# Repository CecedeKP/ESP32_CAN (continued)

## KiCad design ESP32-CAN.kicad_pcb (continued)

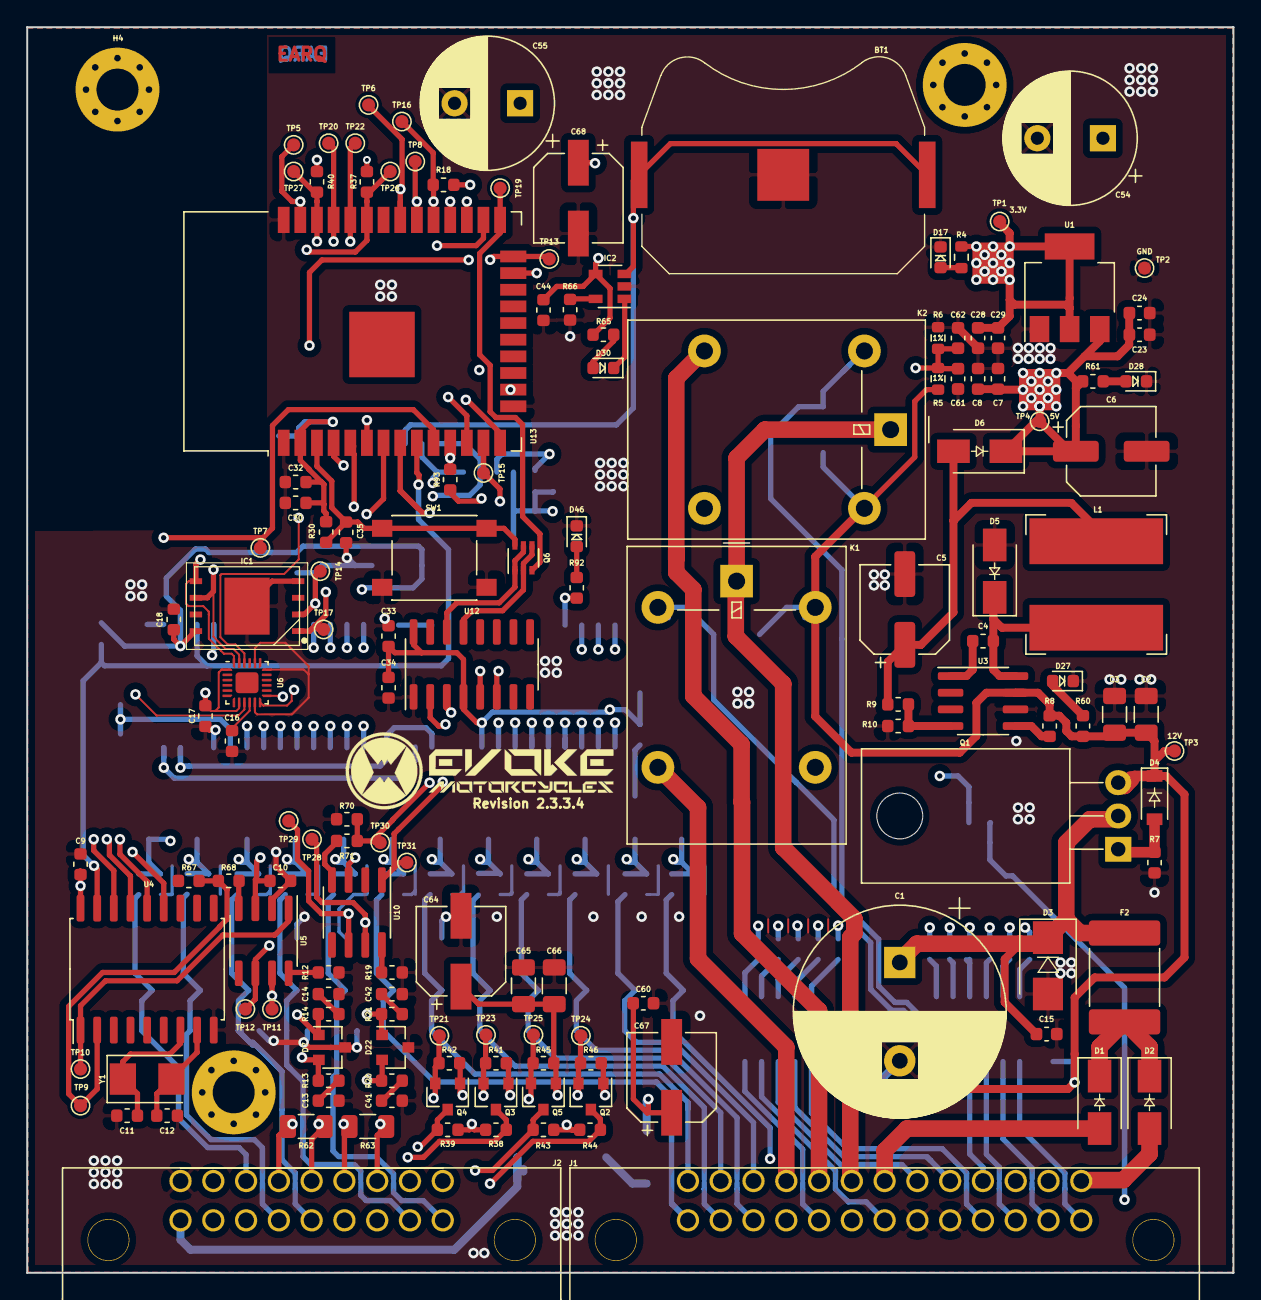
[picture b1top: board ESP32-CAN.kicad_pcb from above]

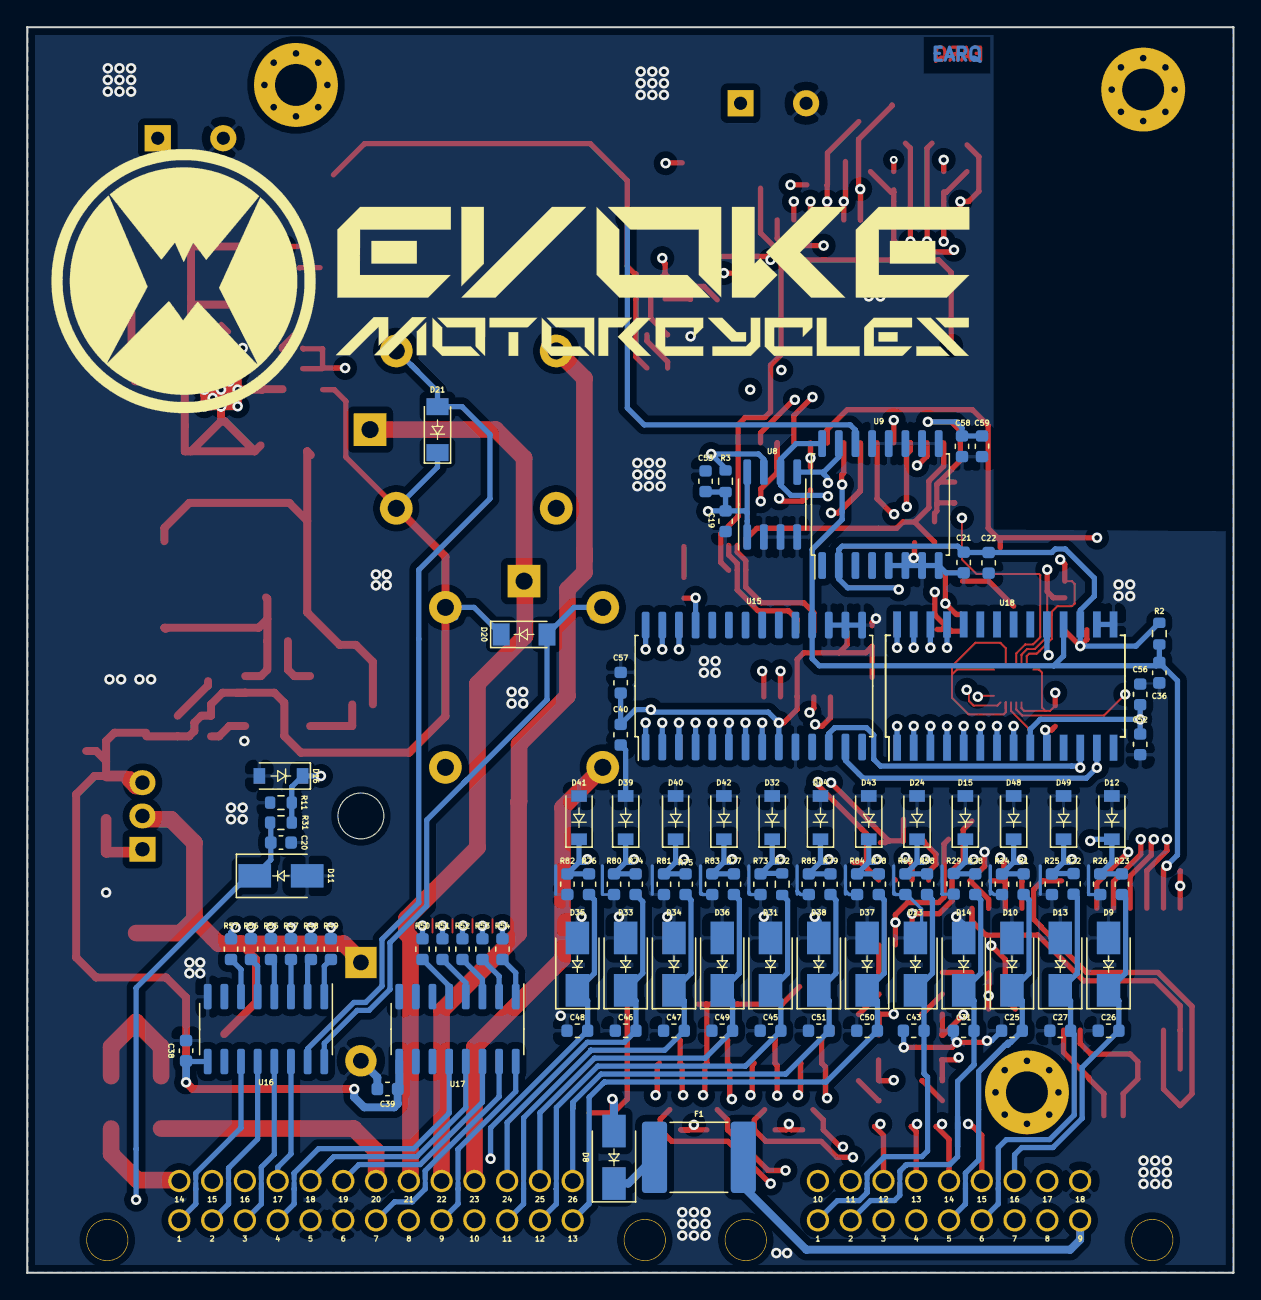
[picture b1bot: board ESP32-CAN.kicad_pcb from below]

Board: 4 copper layers, 92.0 x 95.0 mm, 249 parts (101 on the bottom side), 138 nets.

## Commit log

2024-05-18 After uploading the file manually
    I couldn't push the files. manually
